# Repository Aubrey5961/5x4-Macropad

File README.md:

This is a programmable 5x4 macropad that uses QMK firmware

Parts Used/Needed:
- Pro Micro for the microcontroller
- 1N4148 diodes
- Mechanical switches

Used Alhenkb's keymaps, then edited it for personal use

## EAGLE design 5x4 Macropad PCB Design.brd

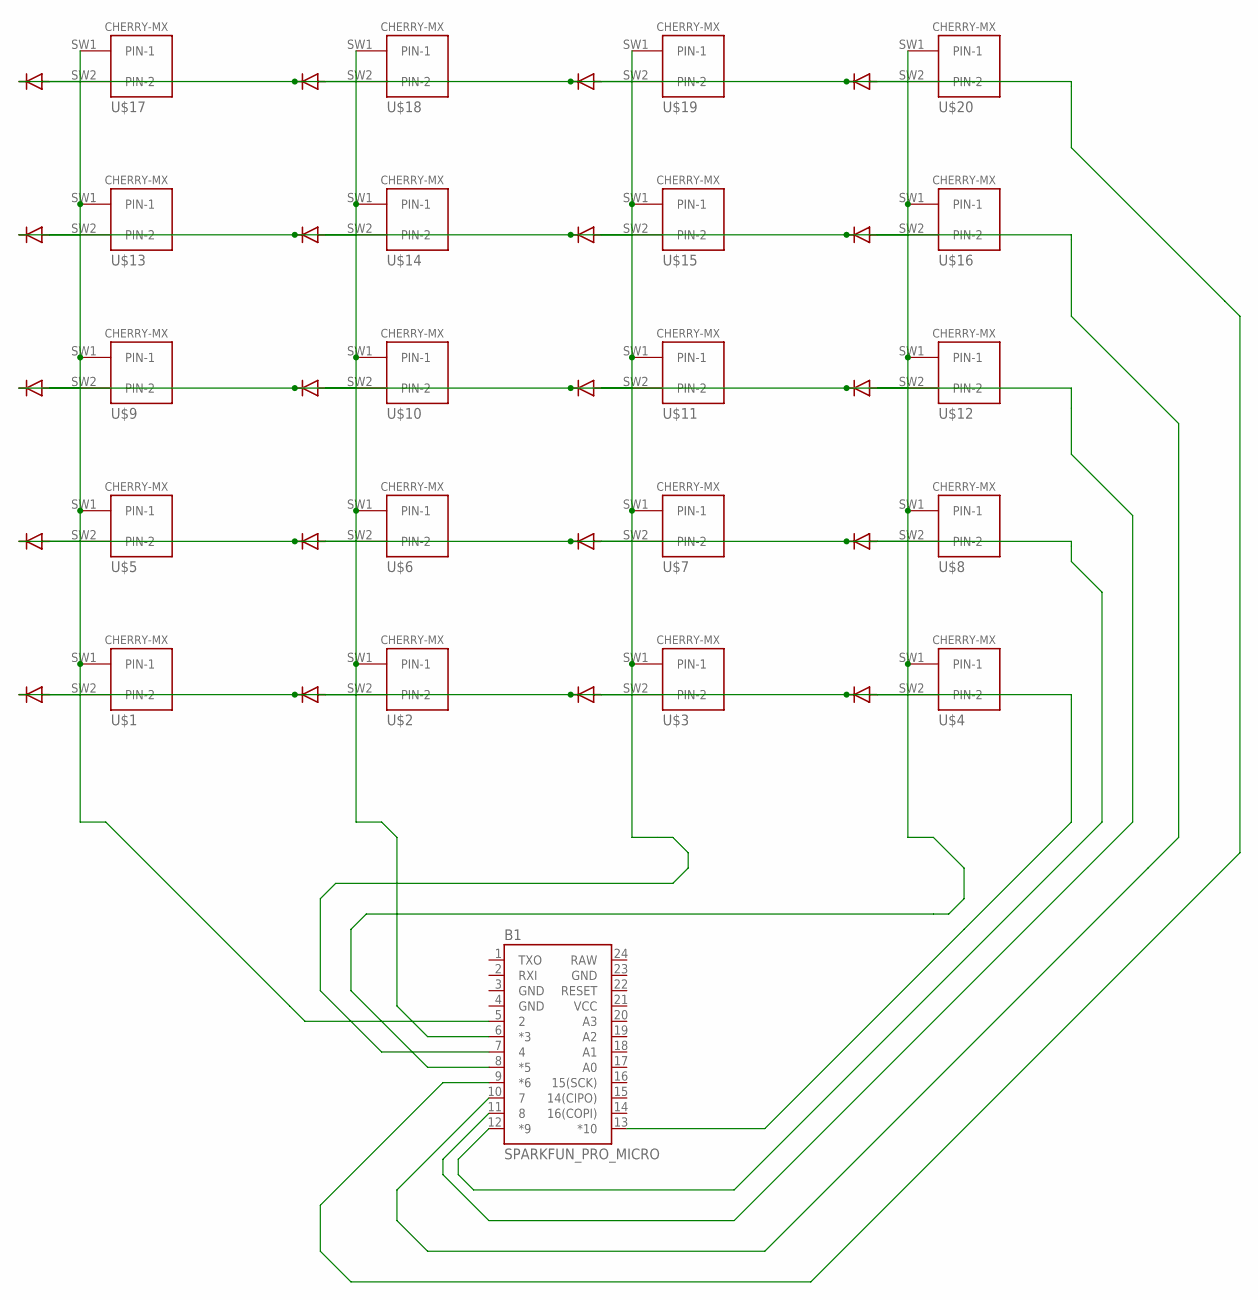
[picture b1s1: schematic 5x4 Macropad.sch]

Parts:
B1: SPARKFUN_PRO_MICRO
D1, D2, D3, D4, D5, D6, D7, D8, D9, D10, D11, D12, D13, D14, D15, D16, D17, D18, D19, D20: 1N4148DO35-10; DO35-10
U$1, U$2, U$3, U$4, U$5, U$6, U$7, U$8, U$9, U$10, U$11, U$12, U$13, U$14, U$15, U$16, U$17, U$18, U$19, U$20: CHERRY-MX

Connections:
GND: B1.3 (GND), B1.4 (GND), B1.23 (GND)
unnamed: D1.A, U$1.SW2 (PIN-2)
unnamed: D2.A, U$2.SW2 (PIN-2)
unnamed: D3.A, U$3.SW2 (PIN-2)
unnamed: D4.A, U$4.SW2 (PIN-2)
unnamed: D5.A, U$5.SW2 (PIN-2)
unnamed: D6.A, U$6.SW2 (PIN-2)
unnamed: D7.A, U$7.SW2 (PIN-2)
unnamed: D8.A, U$8.SW2 (PIN-2)
unnamed: D9.A, U$9.SW2 (PIN-2)
unnamed: D10.A, U$10.SW2 (PIN-2)
unnamed: D11.A, U$11.SW2 (PIN-2)
unnamed: D12.A, U$12.SW2 (PIN-2)
unnamed: D13.A, U$13.SW2 (PIN-2)
unnamed: D14.A, U$14.SW2 (PIN-2)
unnamed: D15.A, U$15.SW2 (PIN-2)
unnamed: D16.A, U$16.SW2 (PIN-2)
unnamed: D17.A, U$17.SW2 (PIN-2)
unnamed: D18.A, U$18.SW2 (PIN-2)
unnamed: D19.A, U$19.SW2 (PIN-2)
unnamed: D20.A, U$20.SW2 (PIN-2)
unnamed: B1.8 (*5), U$4.SW1 (PIN-1), U$8.SW1 (PIN-1), U$12.SW1 (PIN-1), U$16.SW1 (PIN-1), U$20.SW1 (PIN-1)
unnamed: B1.7 (4), U$3.SW1 (PIN-1), U$7.SW1 (PIN-1), U$11.SW1 (PIN-1), U$15.SW1 (PIN-1), U$19.SW1 (PIN-1)
unnamed: B1.6 (*3), U$2.SW1 (PIN-1), U$6.SW1 (PIN-1), U$10.SW1 (PIN-1), U$14.SW1 (PIN-1), U$18.SW1 (PIN-1)
unnamed: B1.5 (2), U$1.SW1 (PIN-1), U$5.SW1 (PIN-1), U$9.SW1 (PIN-1), U$13.SW1 (PIN-1), U$17.SW1 (PIN-1)
unnamed: B1.9 (*6), D17.C, D18.C, D19.C, D20.C
unnamed: B1.10 (7), D13.C, D14.C, D15.C, D16.C
unnamed: B1.11 (8), D9.C, D10.C, D11.C, D12.C
unnamed: B1.12 (*9), D5.C, D6.C, D7.C, D8.C
unnamed: B1.13 (*10), D1.C, D2.C, D3.C, D4.C
RAW: B1.24 (RAW)
VCC: B1.21 (VCC)

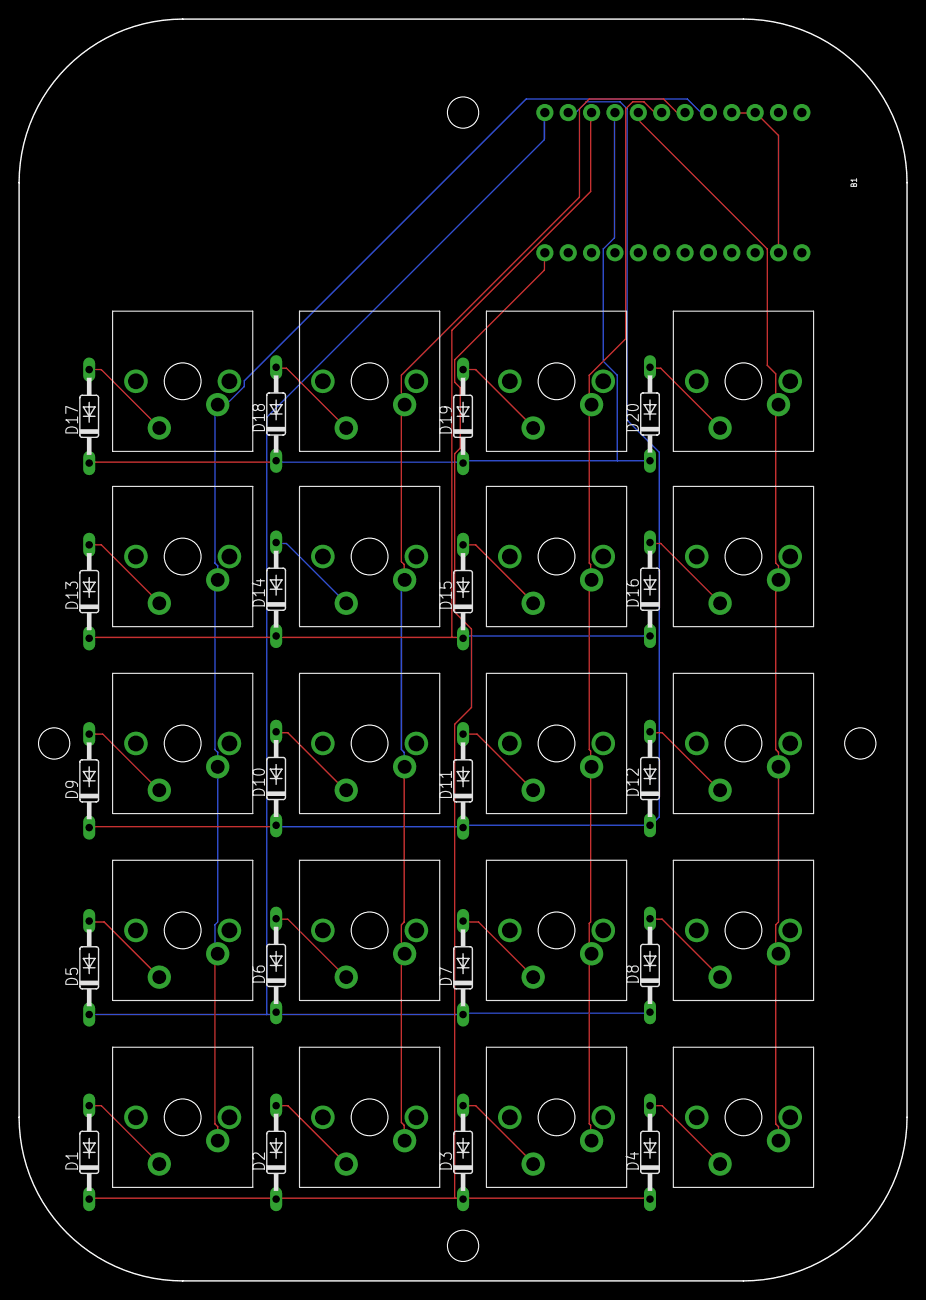
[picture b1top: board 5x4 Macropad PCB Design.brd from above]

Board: 2 copper layers, 96.5 x 137.2 mm, 41 parts (0 on the bottom side), 30 nets.

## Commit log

2025-09-03 Programmable 5x4 Macropad
2025-09-03 Programmable 5x4 Macropad with Pro Micro
2025-09-03 Created README.md

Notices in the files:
parts and their libraries:
SparkFun-Boards: Licensing: Creative Commons ShareAlike 4.0 International - https://creativecommons.org/licenses/by-sa/4.0
